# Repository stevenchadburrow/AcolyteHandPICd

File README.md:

<b>Acolyte - Hand PIC'd</b>

This is a PIC-only version of the Acolyte computer.  The main two chips used are the PIC18F47J13 microcontroller and the XC9572XL CPLD.  It contains 32KB of video RAM and has two Sega Genesis controller ports and a PS/2 keyboard port.  The PIC runs off of a 40 MHz oscillator, yet the video is divided down to 5 MHz.  It displays 4 colors per row from 16 total colors, at a resolution of 400 x 256, or 16 colors per row at 200 x 256.

The main reason for leaving the 6502 / 65816 microprocessor is that the PIC allows you to program in C.  Although I have become pretty good at programming in 6502 assembly, I prefer using C because it is 'my native language'.  The goal for this project is to make a fairly cheap, stand-alone computer that will play (multiplayer) video games, like two-player Tetris.  

I am already thinking of additional upgrades though!  I recently added an audio breakout board, so it is now capable of making simple sound effects.  I also added an SDcard and have been able to re-write the flash memory in the PIC with code from the SDcard.

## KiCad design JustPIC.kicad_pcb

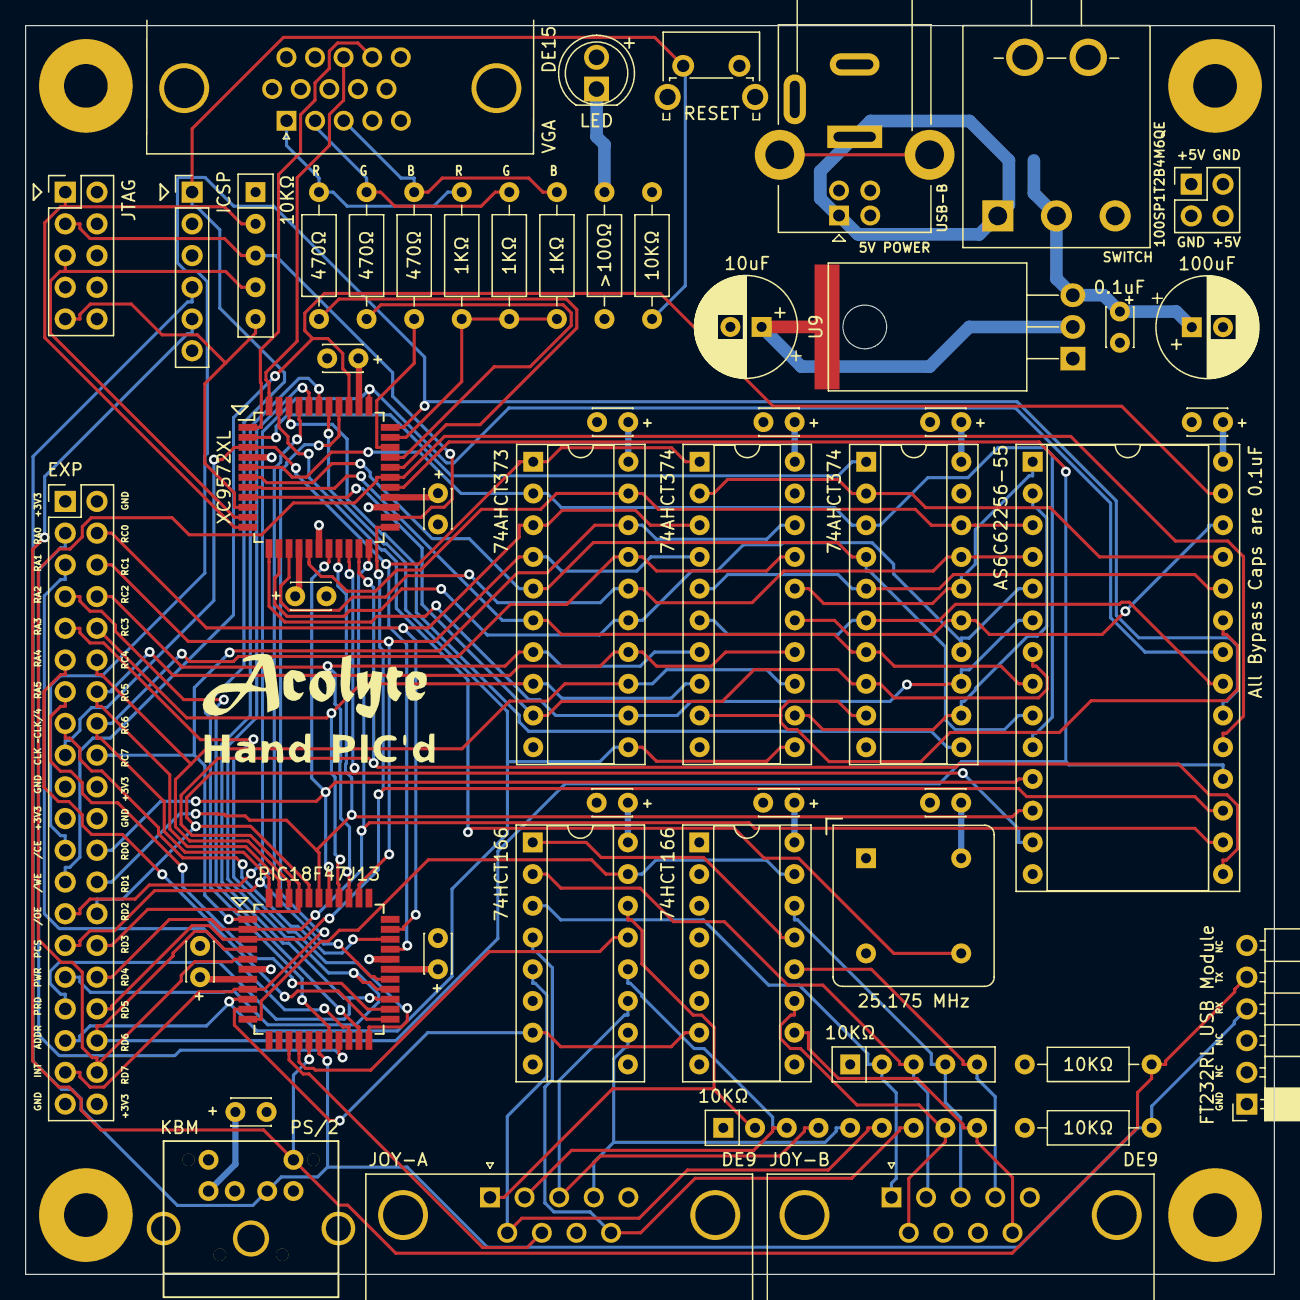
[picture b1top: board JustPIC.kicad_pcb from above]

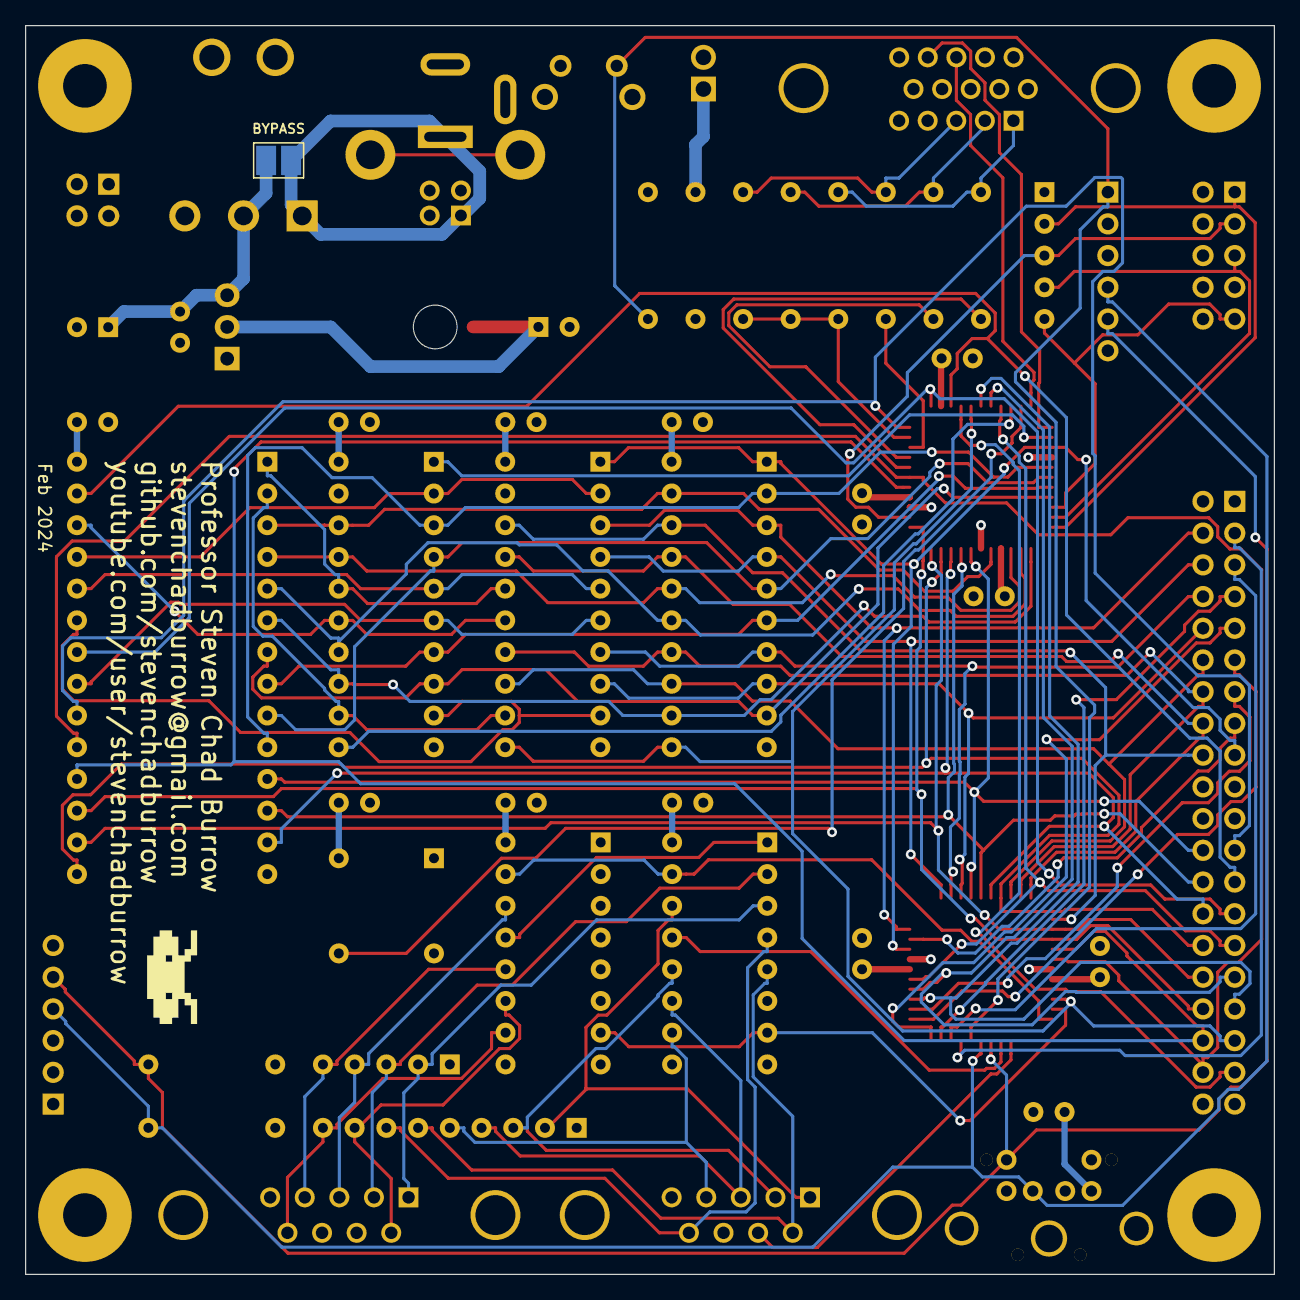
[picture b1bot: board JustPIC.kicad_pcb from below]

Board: 4 copper layers, 100.0 x 100.0 mm, 60 parts (2 on the bottom side), 88 nets.

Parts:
C1, C2, C3, C8, C9, C10, C12, C15, C16, C20, C22, C23, C24, C26: C_Small; C_Disc_D3.0mm_W2.0mm_P2.50mm
C25: C_Polarized_US; CP_Radial_D8.0mm_P2.50mm
C27: C_Polarized_Small_US; CP_Radial_D8.0mm_P2.50mm
D1: LED; CustomLED
G100: LOGO; AcolyteTitle
G101: LOGO; HandPickedTitle
G102: LOGO; Mystery
J1: DE15_Receptacle_HighDensity; DSUB-15-HD_Female_Horizontal_P2.29x2.54mm_VGA
J2, J3: DE9_Plug; DSUB-9_Male_Horizontal_P2.77x2.84mm_EdgePinOffset7.70mm_Hou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
J4: DualPower_USB_B; DualPowerSupply
J5: Mini-DIN-6; PS2_Din6
J6: Conn_02x20_Odd_Even; PinHeader_2x20_P2.54mm_Vertical
J7: Conn_02x05_Odd_Even; PinHeader_2x05_P2.54mm_Vertical
J8: Conn_01x06; PinHeader_1x06_P2.54mm_Vertical
J9: Conn_02x02_Odd_Even; PinHeader_2x02_P2.54mm_Vertical
J10: Conn_01x06; PinSocket_1x06_P2.54mm_Horizontal
JP1: SolderJumper_2_Open; BIG_SolderJumper-2_P1.3mm_Open_Pad1.0x1.5mm
R1, R2, R3, R4, R5, R6, R7, R8, R9, R10: R_US; R_Axial_DIN0207_L6.3mm_D2.5mm_P10.16mm_Horizontal
RN1, RN4: R_Network04_US; R_Array_SIP5
RN2: R_Network08_US; R_Array_SIP9
SW1: SW_SPDT; SPDT-100SP1T2B4M6QE
SW2: SW_Push; SW_Tactile_SPST_Angled_PTS645Vx83-2LFS
TP1, TP2, TP3, TP4: TestPoint; ScrewHole-4-40
U1: AS6C62256-55; DIP-28_W15.24mm_Socket
U2: XC9572VQ44; TQFP-44_10x10mm_P0.8mm
U3: PIC18F47J13; TQFP-44_10x10mm_P0.8mm
U4, U5: 74AHCT374; DIP-20_W7.62mm_Socket
U6: 74AHCT373; DIP-20_W7.62mm_Socket
U7, U8: 74HCT166; DIP-16_W7.62mm_Socket
U9: LM1117T-3.3; TO-220-3_Horizontal_TabDown-custom
X1: CXO_DIP8; Oscillator_DIP-8

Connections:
+3.3V: C8.2, C12.2, C16.2, C20.2, C24.2, C27.1, D1.2 (A), J6.1, J6.20, J6.21, J6.40, J7.4, J8.2, RN1.1 (common), U2.15 (VCC-P21), U2.26 (VCCIO-P32), U2.35 (VCC-P41), U3.7 (VDD), U3.28 (VDD), U9.2 (VO)
+5V: C1.2, C2.2, C3.2, C9.2, C10.2, C15.2, C22.2, C23.2, C25.1, C26.2, J2.5, J3.5, J5.4, J9.1, J9.4, JP1.2 (B), R8.2, R9.1, R10.1, RN2.1 (common), RN4.1 (common), SW1.2 (B), U1.28 (VCC), U4.20 (VCC), U5.20 (VCC), U6.20 (VCC), U7.1 (Ds), U7.2 (A), U7.3 (B), U7.4 (C), U7.5 (D), U7.9 (Clr), U7.16 (VCC), U8.9 (Clr), U8.16 (VCC), U9.3 (VI), X1.8 (Vcc)
/A0: U1.10 (A0), U2.5 (P11), U5.3 (D0), U6.2 (O0)
/A1: U1.9 (A1), U2.6 (P12), U5.4 (D1), U6.5 (O1)
/A2: U1.8 (A2), U2.7 (P13), U5.7 (D2), U6.6 (O2)
/A3: U1.7 (A3), U2.8 (P14), U5.8 (D3), U6.9 (O3)
/A4: U1.6 (A4), U2.12 (P18), U5.13 (D4), U6.12 (O4)
/A5: U1.5 (A5), U2.13 (P19), U5.14 (D5), U6.15 (O5)
/A6: U1.4 (A6), U2.14 (P20), U5.17 (D6), U6.16 (O6)
/A7: U1.3 (A7), U2.16 (P22), U5.18 (D7), U6.19 (O7)
/A8: U1.25 (A8), U4.2 (O0), U5.2 (O0)
/A9: U1.24 (A9), U4.5 (O1), U5.5 (O1)
/A10: U1.21 (A10), U4.6 (O2), U5.6 (O2)
/A11: U1.23 (A11), U4.9 (O3), U5.9 (O3)
/A12: U1.2 (A12), U4.12 (O4), U5.12 (O4)
/A13: U1.26 (A13), U4.15 (O5), U5.15 (O5)
/A14: U1.1 (A14), U4.16 (O6), U5.16 (O6)
/D0: J6.24, U1.11 (Q0), U2.18 (P24), U3.38 (RD0*)
/D1: J6.26, U1.12 (Q1), U2.19 (P25), U3.39 (RD1*)
/D2: J6.28, U1.13 (Q2), U2.20 (P26), U3.40 (RD2*)
/D3: J6.30, U1.15 (Q3), U2.21 (P27), U3.41 (RD3*)
/D4: J6.32, U1.16 (Q4), U2.22 (P28), U3.2 (RD4*)
/D5: J6.34, U1.17 (Q5), U2.23 (P29), U3.3 (RD5*)
/D6: J6.36, U1.18 (Q6), U2.27 (P33), U3.4 (RD6*)
/D7: J6.38, U1.19 (Q7), U2.28 (P34), U3.5 (RD7*)
/P0: J6.4, U3.32 (RC0), U4.3 (D0), U6.3 (D0)
/P1: J6.6, U3.35 (RC1), U4.4 (D1), U6.4 (D1)
/P2: J6.8, U3.36 (RC2), U4.7 (D2), U6.7 (D2)
/P3: J6.10, U3.37 (RC3*), U4.8 (D3), U6.8 (D3)
/P4: J6.12, U3.42 (RC4*), U4.13 (D4), U6.13 (D4)
/P5: J6.14, U3.43 (RC5*), U4.14 (D5), U6.14 (D5)
/P6: J6.16, U3.44 (TX/RC6*), U4.17 (D6), U6.17 (D6)
/P7: J6.18, U3.1 (RX/RC7*), U4.18 (D7), U6.18 (D7)
ADDR: J6.35, U2.38 (P44), U3.9 (RB1), U4.11 (Cp), U6.11 (LE)
BLUE: J1.3, R4.2, R7.2
BLUE-PIX: R4.1, U2.31 (P37)
GND: C1.1, C2.1, C3.1, C8.1, C9.1, C10.1, C12.1, C15.1, C16.1, C20.1, C22.1, C23.1, C24.1, C25.2, C26.1, C27.2, J1.5, J1.6, J1.7, J1.8, J1.10, J2.8, J3.8, J4.4 (GND), J4.7, J5.3, J6.2, J6.19, J6.22, J6.39, J7.2, J7.10, J8.3, J9.2, J9.3, J10.1, R1.2, SW2.2, TP1.1, TP2.1, TP3.1, TP4.1, U1.14 (GND), U2.4 (GND-P10), U2.17 (GND-P23), U2.25 (GND-P31), U3.6 (VSS), U3.29 (VSS), U4.10 (GND), U5.10 (GND), U6.10 (GND), U7.6 (CE), U7.8 (GND), U8.6 (CE), U8.8 (GND), U9.1 (GND), X1.4 (GND)
GPIO0: J6.3, U3.19 (RA0/AN0)
GPIO1: J6.5, U3.20 (RA1/AN1)
GPIO2: J6.7, U3.21 (RA2/AN2)
GPIO3: J6.9, U3.22 (RA3/AN3)
GPIO4: J6.11, U3.23 (RA4/AN4)
GPIO5: J6.13, U3.24 (RA5/AN5)
GREEN: J1.2, R3.2, R6.2
GREEN-PIX: R3.1, U2.30 (P36)
H-SYNC: J1.13, U2.44 (P6-GCK2)
INT-PIX: R5.1, R6.1, R7.1, U2.32 (P38)
JOY-BUTTON1-A: J2.6, RN2.6 (R5), U8.5 (D)
JOY-BUTTON1-B: J3.6, RN2.8 (R7), U7.11 (F)
JOY-BUTTON2-A: J2.9, RN2.7 (R6), U8.4 (C)
JOY-BUTTON2-B: J3.9, RN2.9 (R8), U7.10 (E)
JOY-CLOCK: U3.10 (RB2), U7.7 (Clk), U8.7 (Clk)
JOY-DATA: U3.15 (RB5*), U8.13 (Qh)
JOY-DOWN-A: J2.2, RN2.3 (R2), U8.12 (G)
JOY-DOWN-B: J3.2, RN4.3 (R2), U8.2 (A)
JOY-LEFT-A: J2.3, RN2.4 (R3), U8.11 (F)
JOY-LEFT-B: J3.3, RN4.4 (R3), U7.14 (H)
JOY-LOAD: U3.11 (RB3), U7.15 (PE), U8.15 (PE)
JOY-NEXT: U7.13 (Qh), U8.1 (Ds)
JOY-RIGHT-A: J2.4, RN2.5 (R4), U8.10 (E)
JOY-RIGHT-B: J3.4, RN4.5 (R4), U7.12 (G)
JOY-SELECT: J2.7, U3.14 (RB4*)
JOY-UP-A: J2.1, RN2.2 (R1), U8.14 (H)
JOY-UP-B: J3.1, RN4.2 (R1), U8.3 (B)
JTAG-TCK: J7.1, RN1.2 (R1), U2.11 (TCK-P17)
JTAG-TDI: J7.9, RN1.5 (R4), U2.9 (TDI-P15)
JTAG-TDO: J7.3, RN1.3 (R2), U2.24 (TDO-P30)
JTAG-TMS: J7.5, RN1.4 (R3), U2.10 (TMS-P16)
LATCH: U2.42 (P4), U5.11 (Cp)
LED: D1.1 (K), R1.1
PCS: J6.29, U2.41 (P3), U3.27 (PMCS/RE2)
POWER: J4.1 (VBUS), J4.6, JP1.1 (A), SW1.1 (A)
PRD: J6.33, U2.39 (P1), U3.25 (PMRD/RE0)
PWR: J6.31, U2.40 (P2), U3.26 (PMWR/RE1)
RED: J1.1, R2.2, R5.2
RED-PIX: R2.1, U2.29 (P35)
RX/ICSP-DAT: J5.1, J8.4, J10.4, R10.2, U3.17 (RB7/PGD*)
TX/ICSP-CLK: J5.5, J8.5, J10.5, R9.2, U3.16 (RB6/PGC*)
V-SYNC: J1.14, U2.1 (P7-GCK3)
VCLK: U2.43 (P5-GCK1), X1.5 (OUT)
VIDEO: U2.2 (P8), U5.1 (OE)
VIDEO/4: J6.15, U3.31 (RA6/OSC2/CLKO)
~CE: J6.23, U1.20 (~CS), U2.33 (P39-GSR)
~MCLR: J8.1, R8.1, SW2.1, U3.18 (Vpp/~MCLR/RE3*)
~OE: J6.27, U1.22 (~OE), U2.34 (P40-GTS2)
~VIDEO: J6.17, U2.3 (P9), U3.30 (RA7/OSC1/CLKI), U4.1 (OE), U6.1 (OE)
~WE: J6.25, U1.27 (~WE), U2.36 (P42-GTS1)
~WRITE: J6.37, U2.37 (P43), U3.8 (RB0/INT0)

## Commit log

2024-03-10 Rename main.c to main_TEST.c
2024-03-10 Rename main_TEST.c to test.c
